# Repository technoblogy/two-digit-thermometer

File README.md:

# Two-Digit Thermometer
A two-digit LED thermometer using a DS12B20 1-Wire temperature sensor, and an ATtiny84 to drive the display and read the sensor. For more information see: http://www.technoblogy.com/show?2G8T.

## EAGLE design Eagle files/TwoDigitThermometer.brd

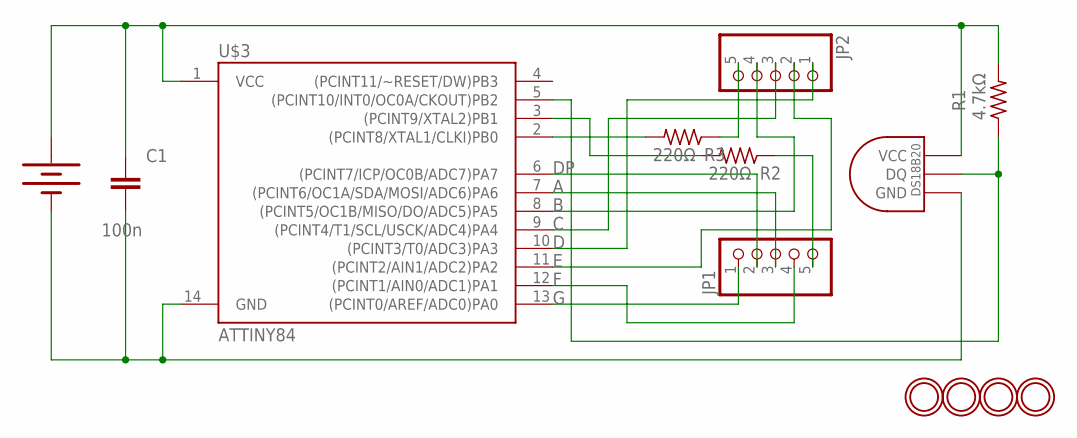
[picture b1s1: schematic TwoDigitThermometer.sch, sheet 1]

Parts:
BAT1: 20mm coincell; BATTCON_20MM
C1: 100n; 0603-CAP
JP1, JP2: HEADER-1X5EDGESMT; 1X05_EDGESMT
R1: 4.7kΩ; R0805
R2, R3: 220Ω; R0805
U$1, U$4, U$5, U$9: MOUNTINGHOLE2.5; MOUNTINGHOLE_2.5_PLATED
U$2: DS1820; µSOP8
U$3: ATTINY84; SO14

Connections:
A: JP1.3, U$3.7 ((PCINT6/OC1A/SDA/MOSI/ADC6)PA6)
B: JP2.4, U$3.8 ((PCINT5/OC1B/MISO/DO/ADC5)PA5)
C: JP2.3, U$3.9 ((PCINT4/T1/SCL/USCK/ADC4)PA4)
D: JP2.1, U$3.10 ((PCINT3/T0/ADC3)PA3)
DP: JP1.2, U$3.6 ((PCINT7/ICP/OC0B/ADC7)PA7)
E: JP2.2, U$3.11 ((PCINT2/AIN1/ADC2)PA2)
F: JP1.4, U$3.12 ((PCINT1/AIN0/ADC1)PA1)
G: JP1.1, U$3.13 ((PCINT0/AREF/ADC0)PA0)
unnamed: BAT1.1 (+), C1.1, R1.2, U$2.8 (VCC), U$3.1 (VCC)
unnamed: R1.1, U$2.1 (DQ), U$3.5 ((PCINT10/INT0/OC0A/CKOUT)PB2)
unnamed: R3.2, U$3.2 ((PCINT8/XTAL1/CLKI)PB0)
unnamed: R2.2, U$3.3 ((PCINT9/XTAL2)PB1)
unnamed: BAT1.2 (-), C1.2, U$2.4 (GND), U$3.14 (GND)
unnamed: JP1.5, R2.1
unnamed: JP2.5, R3.1

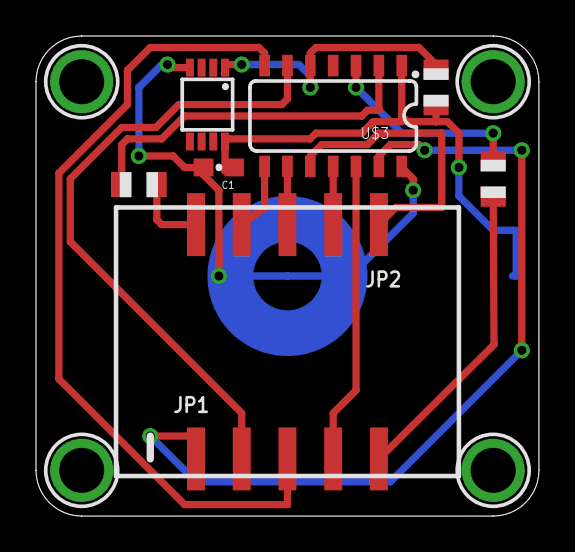
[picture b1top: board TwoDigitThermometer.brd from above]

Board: 2 copper layers, 27.9 x 26.7 mm, 13 parts (1 on the bottom side), 15 nets.

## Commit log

2019-04-09 Version 1 - 9th April 2019

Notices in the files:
parts and their libraries:
SparkFun-Capacitors: Licensing: CC v3.0 Share-Alike You are welcome to use this library for commercial purposes.
SparkFun-Electromechanical: Licensing: Creative Commons ShareAlike 4.0 International - https://creativecommons.org/licenses/by-sa/4.0
